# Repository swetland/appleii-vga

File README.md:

# Apple II VGA PCB

This is a pair of PCBs that implements a version of the Apple II VGA design.

Please see the [Apple II VGA Project](https://github.com/markadev/AppleII-VGA) for details and firmware.

This version differs from the original in that:
1. It makes use of the Rpi Pico's regulator for 3v3 supply
2. It allows the SYNC signal to be optionally routed to the Rpi Pico (instead of allowing Apple II bus read operations)
3. It uses a fourth 74LVC245A instead of a 74LS07 for the remaining bus signals (fewer unique components)

The KiCAD source files are included in the [appleii.vga/](appleii.vga/)
and [appleii.vga.connector/](appleii.vga.connector/) directories.

The [export/](export/) directory contains gerber files suitable for fabrication.
Beware that only the v1.0.2 version has been fabricated so far (at JLCPCB).
The v1.1.0 version contains some minor improvements but has not yet been
fabricated and tested.

To use the standard firmware, install a 0 ohm resistor at R13 and leave R12 and R14 unpopulated.

PCBs and parts for assembly:

Assembled PCBs:

Installed in an Apple IIe:

Lode Runner displayed on a 15" Sony Trinitron VGA monitor:

Schematic and Layout for v1.1.0:

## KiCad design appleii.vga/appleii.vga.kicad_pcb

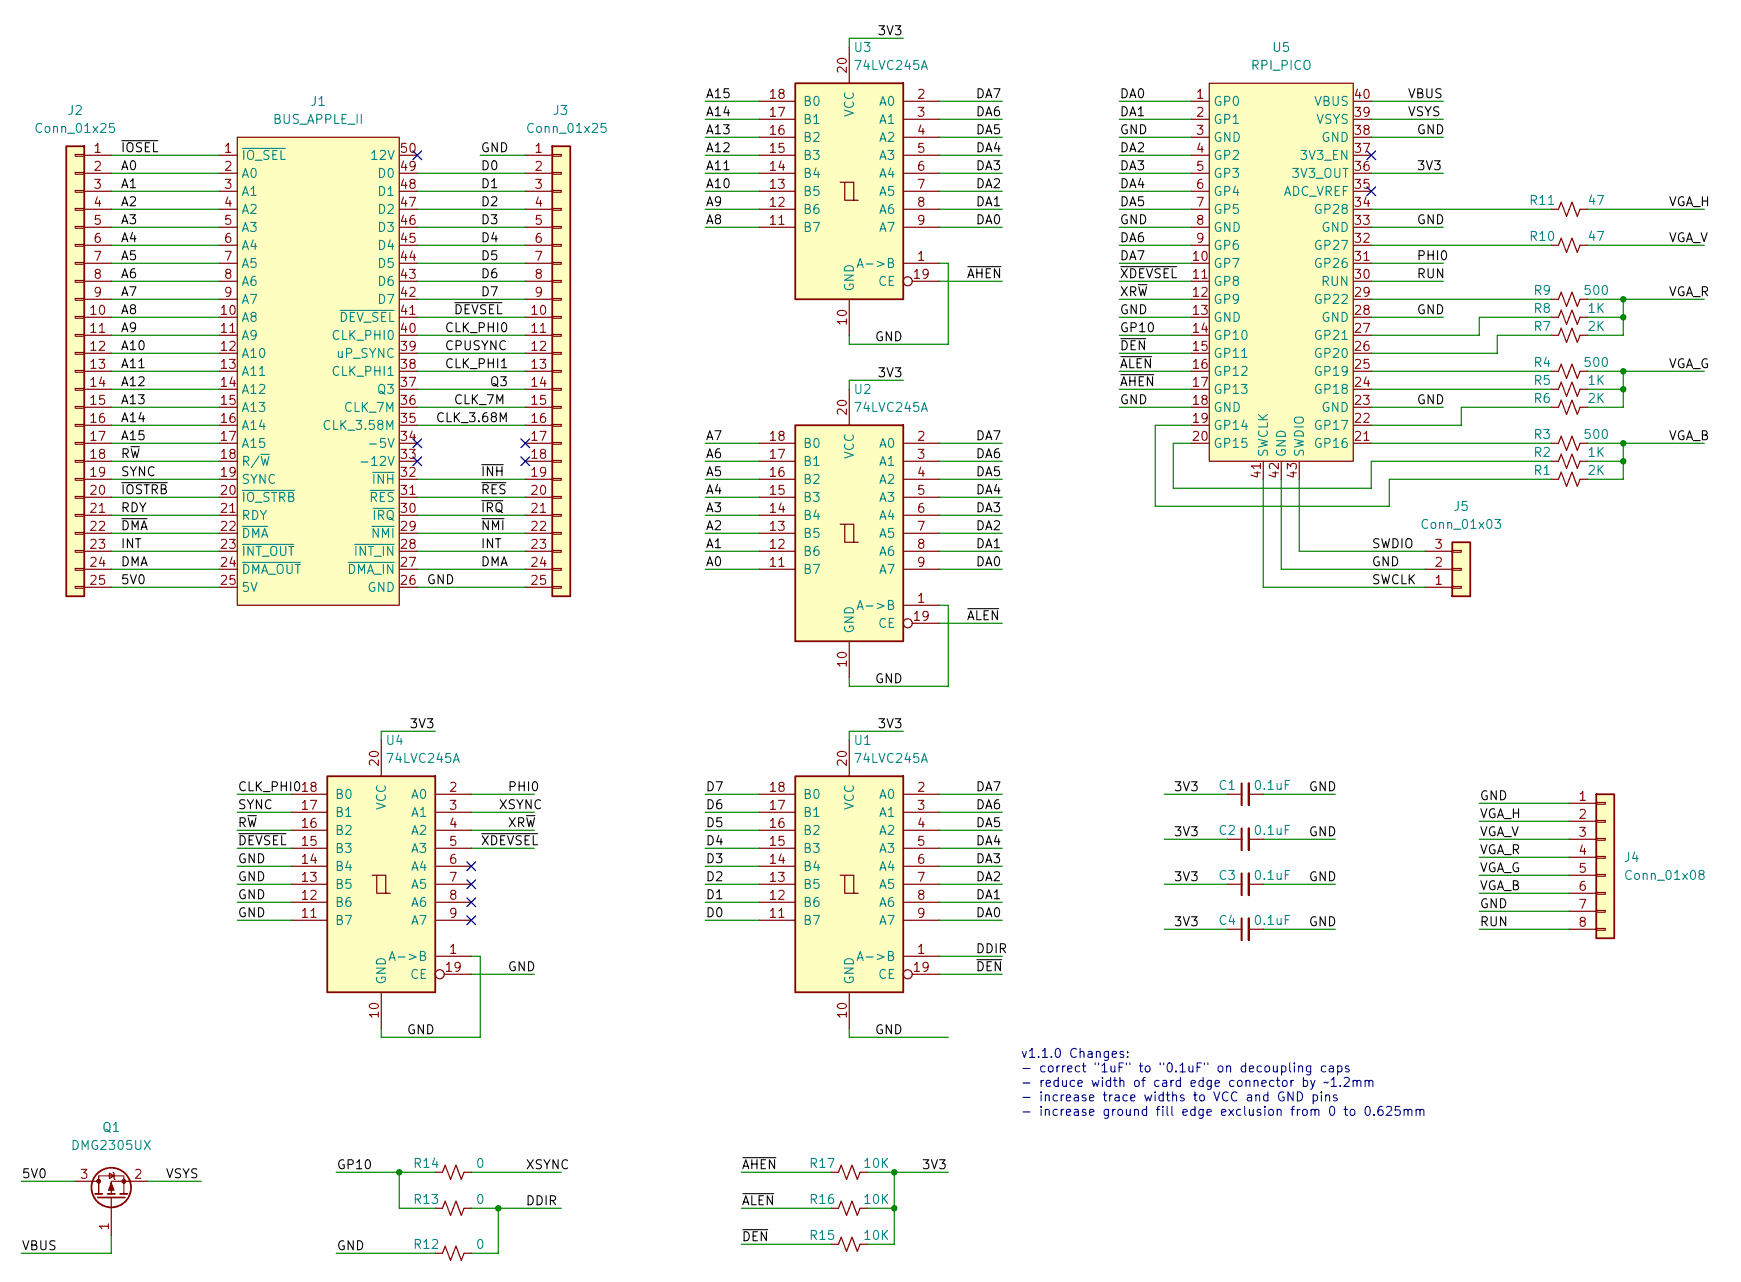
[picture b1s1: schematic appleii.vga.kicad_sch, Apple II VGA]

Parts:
C1, C2, C3, C4: 0.1uF; C_0603_1608Metric_Pad1.08x0.95mm_HandSolder
J1: BUS_APPLE_II
J2, J3: Conn_01x25; PinHeader_1x25_P2.54mm_Vertical
J4: Conn_01x08; PinHeader_1x08_P2.54mm_Vertical
J5: Conn_01x03; PinHeader_1x03_P2.54mm_Vertical
Q1: DMG2305UX; SOT-23_Handsoldering
R1, R6, R7: 2K; R_0603_1608Metric_Pad0.98x0.95mm_HandSolder
R2, R5, R8: 1K; R_0603_1608Metric_Pad0.98x0.95mm_HandSolder
R3, R4, R9: 500; R_0603_1608Metric_Pad0.98x0.95mm_HandSolder
R10, R11: 47; R_0603_1608Metric_Pad0.98x0.95mm_HandSolder
R12, R13, R14: 0; R_0603_1608Metric_Pad0.98x0.95mm_HandSolder
R15, R16, R17: 10K; R_0603_1608Metric_Pad0.98x0.95mm_HandSolder
U1, U2, U3, U4: 74LVC245A; SOIC-20W_7.5x12.8mm_P1.27mm
U5: RPI_PICO

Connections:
/3V3: C1.1, C2.1, C3.1, C4.1, R15.2, R16.2, R17.2, U1.20 (VCC), U2.20 (VCC), U3.20 (VCC), U4.20 (VCC), U5.36 (3V3_OUT)
/5V0: J1.25 (5V), J2.25, Q1.3 (D)
/A0: J1.2 (A0), J2.2, U2.11 (B7)
/A1: J1.3 (A1), J2.3, U2.12 (B6)
/A2: J1.4 (A2), J2.4, U2.13 (B5)
/A3: J1.5 (A3), J2.5, U2.14 (B4)
/A4: J1.6 (A4), J2.6, U2.15 (B3)
/A5: J1.7 (A5), J2.7, U2.16 (B2)
/A6: J1.8 (A6), J2.8, U2.17 (B1)
/A7: J1.9 (A7), J2.9, U2.18 (B0)
/A8: J1.10 (A8), J2.10, U3.11 (B7)
/A9: J1.11 (A9), J2.11, U3.12 (B6)
/A10: J1.12 (A10), J2.12, U3.13 (B5)
/A11: J1.13 (A11), J2.13, U3.14 (B4)
/A12: J1.14 (A12), J2.14, U3.15 (B3)
/A13: J1.15 (A13), J2.15, U3.16 (B2)
/A14: J1.16 (A14), J2.16, U3.17 (B1)
/A15: J1.17 (A15), J2.17, U3.18 (B0)
/CLK_3.68M: J1.35 (CLK_3.58M), J3.16
/CLK_7M: J1.36 (CLK_7M), J3.15
/CLK_PHI0: J1.40 (CLK_PHI0), J3.11, U4.18 (B0)
/CLK_PHI1: J1.38 (CLK_PHI1), J3.13
/CPUSYNC: J1.39 (uP_SYNC), J3.12
/D0: J1.49 (D0), J3.2, U1.11 (B7)
/D1: J1.48 (D1), J3.3, U1.12 (B6)
/D2: J1.47 (D2), J3.4, U1.13 (B5)
/D3: J1.46 (D3), J3.5, U1.14 (B4)
/D4: J1.45 (D4), J3.6, U1.15 (B3)
/D5: J1.44 (D5), J3.7, U1.16 (B2)
/D6: J1.43 (D6), J3.8, U1.17 (B1)
/D7: J1.42 (D7), J3.9, U1.18 (B0)
/DA0: U1.9 (A7), U2.9 (A7), U3.9 (A7), U5.1 (GP0)
/DA1: U1.8 (A6), U2.8 (A6), U3.8 (A6), U5.2 (GP1)
/DA2: U1.7 (A5), U2.7 (A5), U3.7 (A5), U5.4 (GP2)
/DA3: U1.6 (A4), U2.6 (A4), U3.6 (A4), U5.5 (GP3)
/DA4: U1.5 (A3), U2.5 (A3), U3.5 (A3), U5.6 (GP4)
/DA5: U1.4 (A2), U2.4 (A2), U3.4 (A2), U5.7 (GP5)
/DA6: U1.3 (A1), U2.3 (A1), U3.3 (A1), U5.9 (GP6)
/DA7: U1.2 (A0), U2.2 (A0), U3.2 (A0), U5.10 (GP7)
/DDIR: R12.2, R13.2, U1.1 (A->B)
/DMA: J1.24 (~DMA_OUT), J1.27 (~DMA_IN), J2.24, J3.24
/GND: C1.2, C2.2, C3.2, C4.2, J1.26 (GND), J3.1, J3.25, J4.1, J4.7, J5.2, R12.1, U1.10 (GND), U2.1 (A->B), U2.10 (GND), U3.1 (A->B), U3.10 (GND), U4.1 (A->B), U4.10 (GND), U4.11 (B7), U4.12 (B6), U4.13 (B5), U4.14 (B4), U4.19 (CE), U5.3 (GND), U5.8 (GND), U5.13 (GND), U5.18 (GND), U5.23 (GND), U5.28 (GND), U5.33 (GND), U5.38 (GND), U5.42 (GND)
/GP10: R13.1, R14.1, U5.14 (GP10)
/INT: J1.23 (~INT_OUT), J1.28 (~INT_IN), J2.23, J3.23
/PHI0: U4.2 (A0), U5.31 (GP26)
/Q3: J1.37 (Q3), J3.14
/RDY: J1.21 (RDY), J2.21
/RUN: J4.8, U5.30 (RUN)
/R~W: J1.18 (R/~W), J2.18, U4.16 (B2)
/SWCLK: J5.1, U5.41 (SWCLK)
/SWDIO: J5.3, U5.43 (SWDIO)
/SYNC: J1.19 (SYNC), J2.19, U4.17 (B1)
/VBUS: Q1.1 (G), U5.40 (VBUS)
/VGA_B: J4.6, R1.2, R2.2, R3.2
/VGA_G: J4.5, R4.2, R5.2, R6.2
/VGA_H: J4.2, R11.2
/VGA_R: J4.4, R7.2, R8.2, R9.2
/VGA_V: J4.3, R10.2
/VSYS: Q1.2 (S), U5.39 (VSYS)
/XR~W: U4.4 (A2), U5.12 (GP9)
/XSYNC: R14.2, U4.3 (A1)
/~AHEN: R17.1, U3.19 (CE), U5.17 (GP13)
/~ALEN: R16.1, U2.19 (CE), U5.16 (GP12)
/~DEN: R15.1, U1.19 (CE), U5.15 (GP11)
/~DEVSEL: J1.41 (~DEV_SEL), J3.10, U4.15 (B3)
/~DMA: J1.22 (~DMA), J2.22
/~INH: J1.32 (~INH), J3.19
/~IOSEL: J1.1 (~IO_SEL), J2.1
/~IOSTRB: J1.20 (~IO_STRB), J2.20
/~IRQ: J1.30 (~IRQ), J3.21
/~NMI: J1.29 (~NMI), J3.22
/~RES: J1.31 (~RES), J3.20
/~XDEVSEL: U4.5 (A3), U5.11 (GP8)
unnamed: R1.1, U5.19 (GP14)
unnamed: R2.1, U5.20 (GP15)
unnamed: R3.1, U5.21 (GP16)
unnamed: R6.1, U5.22 (GP17)
unnamed: R5.1, U5.24 (GP18)
unnamed: R4.1, U5.25 (GP19)
unnamed: R7.1, U5.26 (GP20)
unnamed: R8.1, U5.27 (GP21)
unnamed: R9.1, U5.29 (GP22)
unnamed: R10.1, U5.32 (GP27)
unnamed: R11.1, U5.34 (GP28)

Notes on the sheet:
v1.1.0 Changes: - correct "1uF" to "0.1uF" on decoupling caps - reduce width of card edge connector by ~1.2mm - increase trace widths to VCC and GND pins - increase ground fill edge exclusion from 0 to 0.625mm

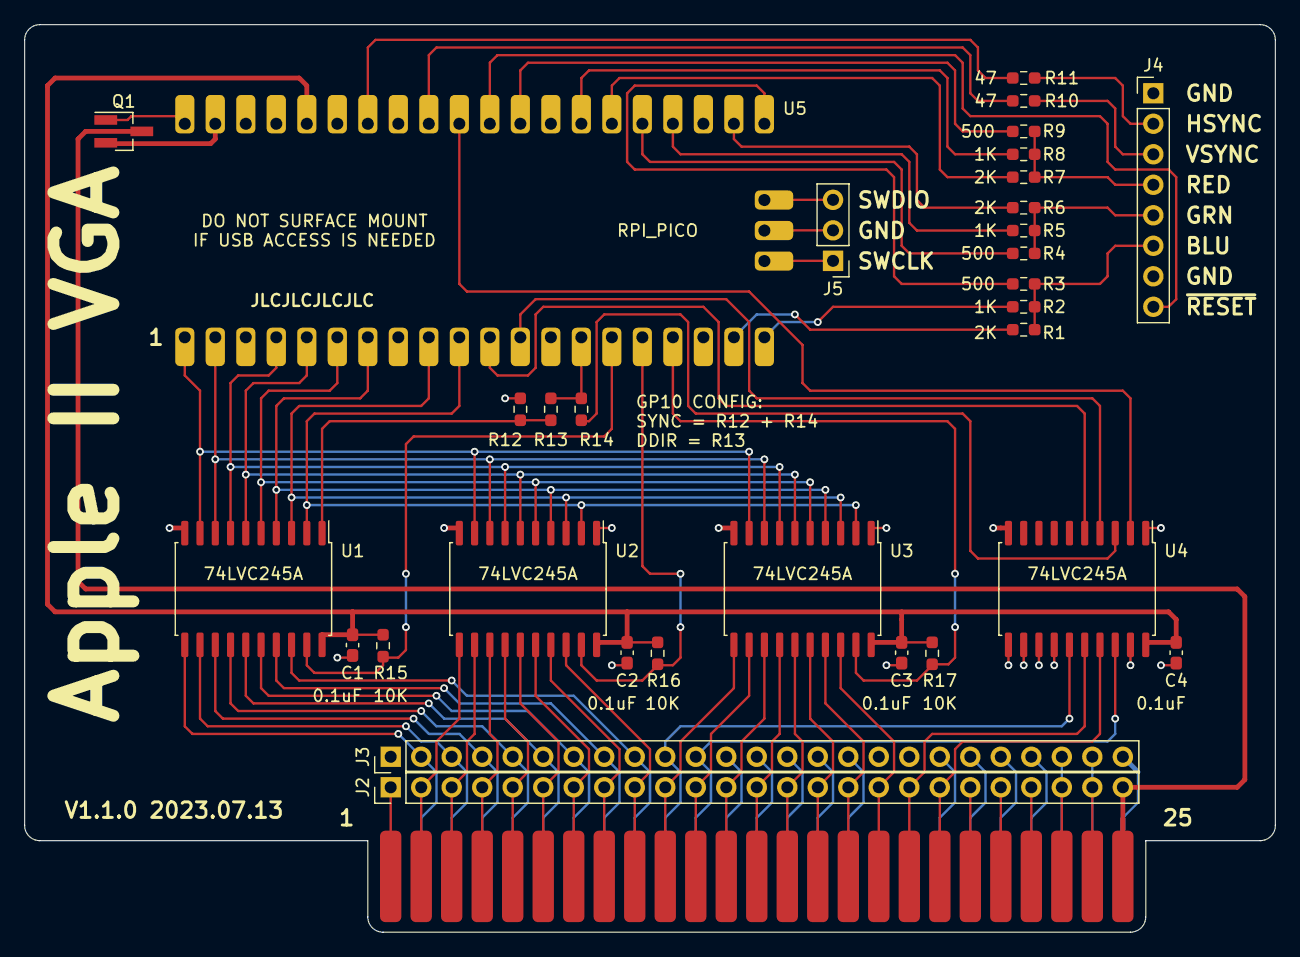
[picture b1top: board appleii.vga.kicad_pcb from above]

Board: 2 copper layers, 104.1 x 75.6 mm, 32 parts (0 on the bottom side), 84 nets.

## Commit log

2023-07-06 initial checkin - v1.0.2
2023-07-06 initial checkin - library
2023-07-06 exported gerbers - v1.0.2
2023-07-06 change schematic page layout to us legal
2023-07-13 upgrade to kicad 7
2023-07-13 update board to v1.1.0
    Some minor improvements based on v1.0.2 fab, assembly and test:
    - correct "1uF" to "0.1uF" on decoupling caps
    - reduce width of card edge connector by ~1.2mm
    - increase trace widths to VCC and GND pins
    - increase ground fill edge exclusion from 0 to 0.625mm
2023-07-13 move items into subdirectories
2023-07-13 add appleii.vga.connector schematic and layout
2023-07-13 add LICENSE (MIT-0)
2023-07-13 update copyright in schematic
2023-07-13 git ignore file
2023-07-13 gerbers for v1.1.0
2023-07-13 fix copper fill edge clearance setting
2023-07-13 add gerbers for connector board
2023-07-13 add pdf and png versions of schematic and layout
2023-07-13 photos
2023-07-13 add a readme file

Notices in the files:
appleii.vga/appleii.vga.kicad_sch:
Licensed under the MIT-0 License
Copyright 2023, Brian Swetland
